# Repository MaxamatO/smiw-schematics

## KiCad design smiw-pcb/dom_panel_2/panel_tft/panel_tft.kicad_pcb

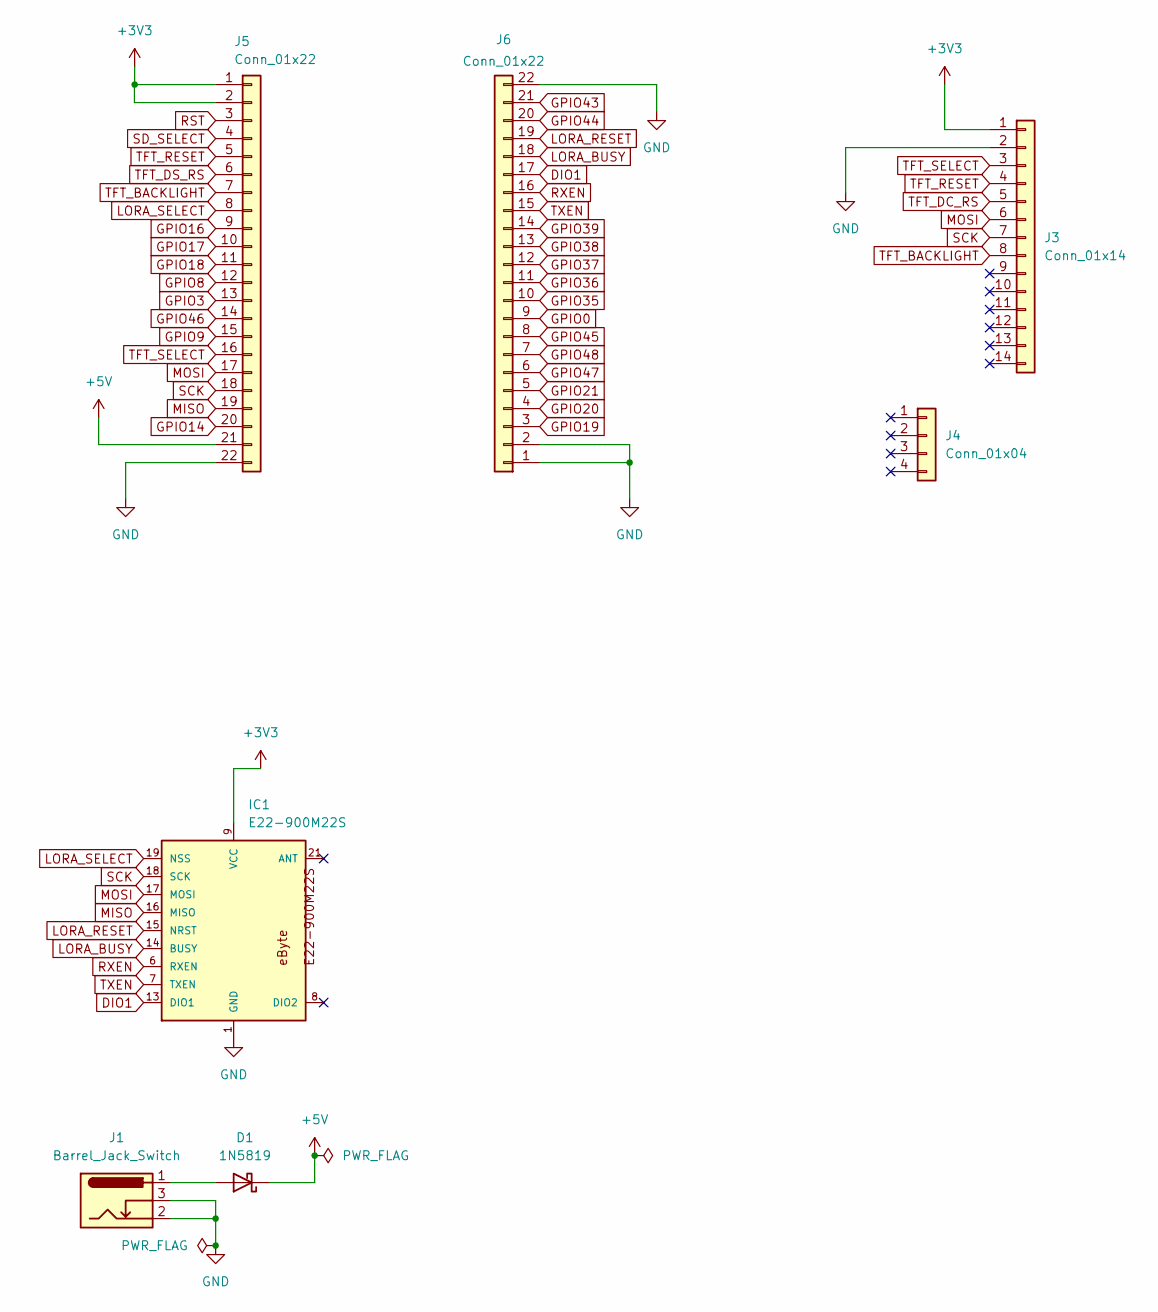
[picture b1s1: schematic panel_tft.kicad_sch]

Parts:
D1: 1N5819; D_DO-41_SOD81_P10.16mm_Horizontal
IC1: E22-900M22S
J1: Barrel_Jack_Switch; BarrelJack_Horizontal
J3: Conn_01x14; PinSocket_1x14_P2.54mm_Vertical
J4: Conn_01x04; PinSocket_1x04_P2.54mm_Vertical
J5, J6: Conn_01x22; PinSocket_1x22_P2.54mm_Vertical

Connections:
+3V3: IC1.9 (VCC), J3.1, J5.1, J5.2
+5V: D1.1 (K), J5.21
DIO1: IC1.13 (DIO1), J6.17
GND: IC1.1 (GND), IC1.2 (GND), IC1.3 (GND), IC1.4 (GND), IC1.5 (GND), IC1.10 (GND), IC1.11 (GND), IC1.12 (GND), IC1.20 (GND), IC1.22 (GND), J1.2, J1.3, J3.2, J5.22, J6.1, J6.2, J6.22
GPIO0: J6.9
GPIO3: J5.13
GPIO8: J5.12
GPIO9: J5.15
GPIO14: J5.20
GPIO16: J5.9
GPIO17: J5.10
GPIO18: J5.11
GPIO19: J6.3
GPIO20: J6.4
GPIO21: J6.5
GPIO35: J6.10
GPIO36: J6.11
GPIO37: J6.12
GPIO38: J6.13
GPIO39: J6.14
GPIO43: J6.21
GPIO44: J6.20
GPIO45: J6.8
GPIO46: J5.14
GPIO47: J6.6
GPIO48: J6.7
LORA_BUSY: IC1.14 (BUSY), J6.18
LORA_RESET: IC1.15 (NRST), J6.19
LORA_SELECT: IC1.19 (NSS), J5.8
MISO: IC1.16 (MISO), J5.19
MOSI: IC1.17 (MOSI), J3.6, J5.17
unnamed: D1.2 (A), J1.1
RST: J5.3
RXEN: IC1.6 (RXEN), J6.16
SCK: IC1.18 (SCK), J3.7, J5.18
SD_SELECT: J5.4
TFT_BACKLIGHT: J3.8, J5.7
TFT_DC_RS: J3.5
TFT_DS_RS: J5.6
TFT_RESET: J3.4, J5.5
TFT_SELECT: J3.3, J5.16
TXEN: IC1.7 (TXEN), J6.15

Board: 2 copper layers, 7 parts (0 on the bottom side), 16 nets, no tracks yet.

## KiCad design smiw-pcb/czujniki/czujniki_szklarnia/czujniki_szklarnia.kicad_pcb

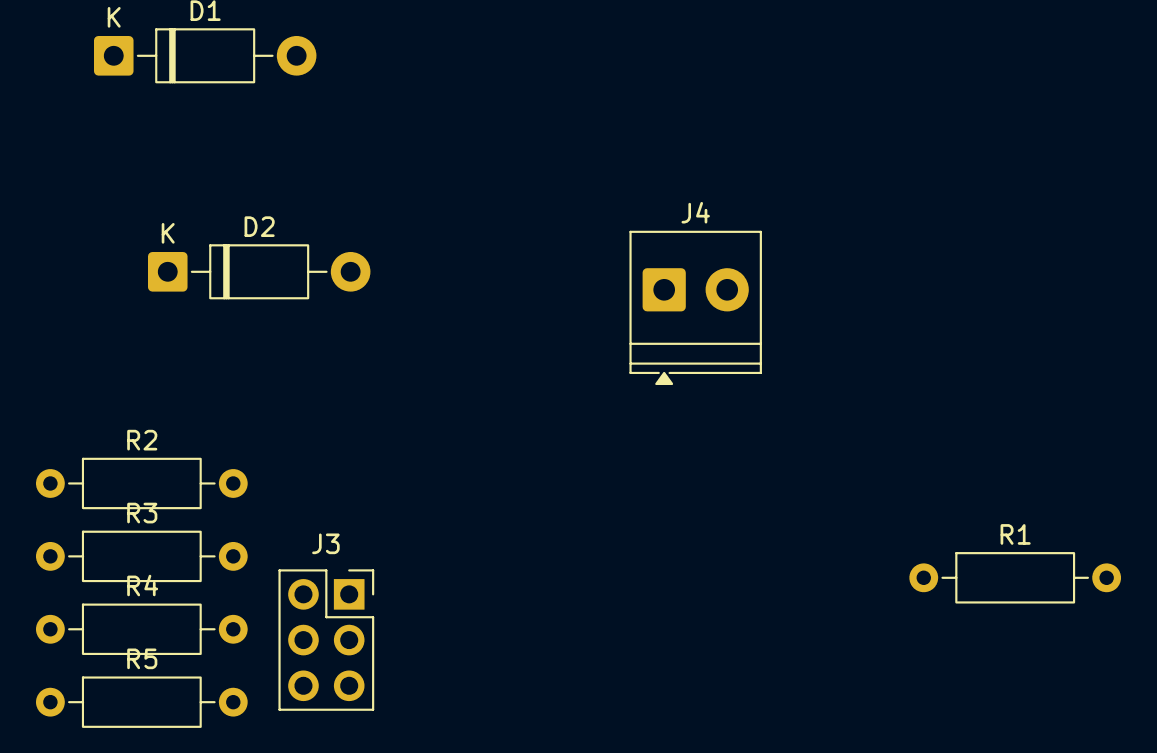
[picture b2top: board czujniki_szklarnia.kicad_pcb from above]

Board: 2 copper layers, 9 parts (0 on the bottom side), 6 nets, no tracks yet.

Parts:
D1, D2: 1N4007; D_DO-41_SOD81_P10.16mm_Horizontal
J3: Conn_02x03_Counter_Clockwise; PinSocket_2x03_P2.54mm_Vertical
J4: Screw_Terminal_01x02; TerminalBlock_Phoenix_PT-1,5-2-3.5-H_1x02_P3.50mm_Horizontal
R1: 4K7; R_Axial_DIN0207_L6.3mm_D2.5mm_P10.16mm_Horizontal
R2, R3: 1K; R_Axial_DIN0207_L6.3mm_D2.5mm_P10.16mm_Horizontal
R4, R5: 100K; R_Axial_DIN0207_L6.3mm_D2.5mm_P10.16mm_Horizontal

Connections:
+3V3: J3.1, R1.2
+24V: D1.1 (K), D2.1 (K)
GND: J3.2, J3.6, R4.1, R5.1
unnamed: R2.2, R5.2
unnamed: R3.2, R4.2
OW: J3.3, R1.1

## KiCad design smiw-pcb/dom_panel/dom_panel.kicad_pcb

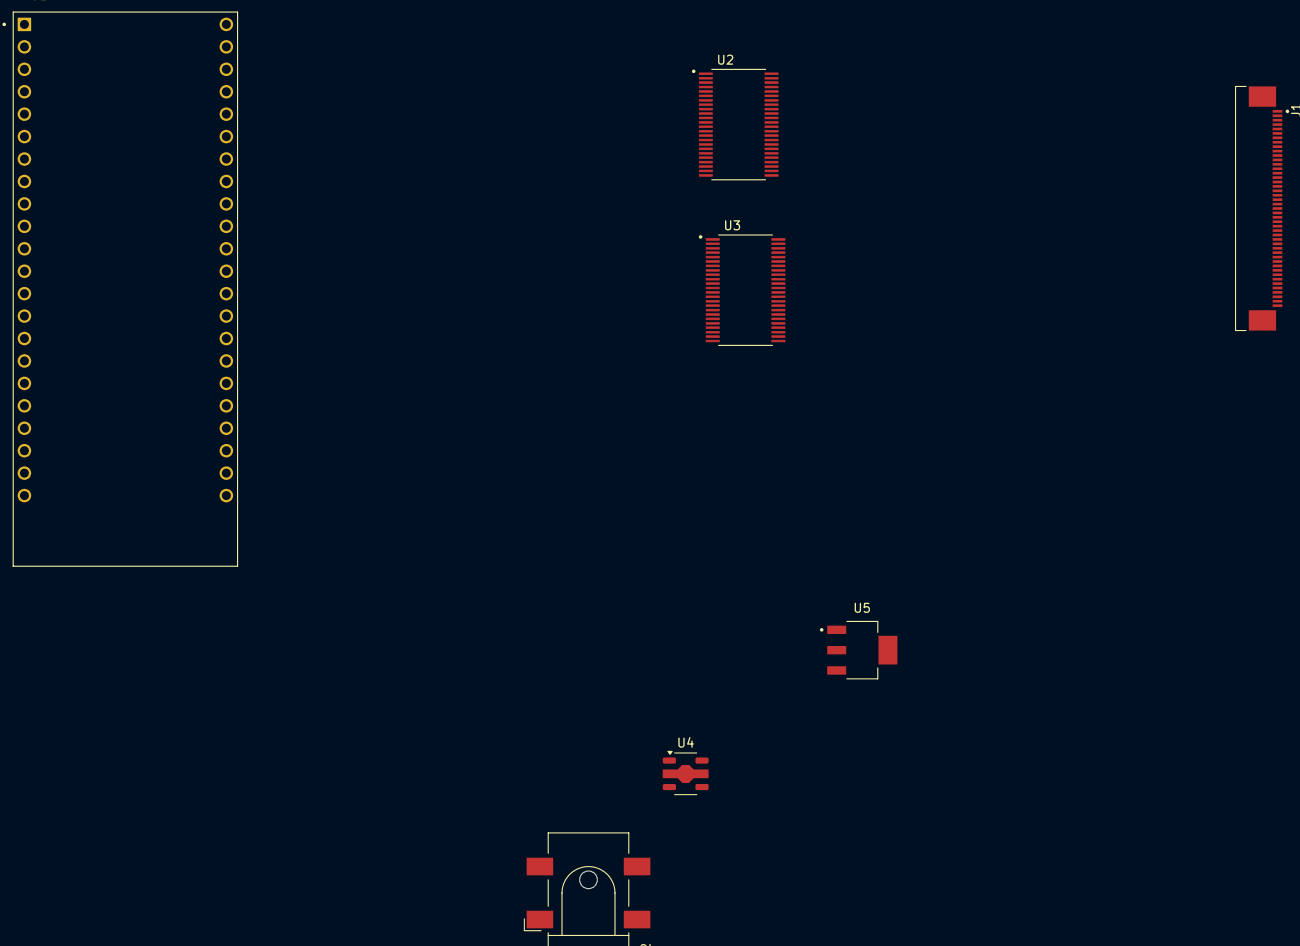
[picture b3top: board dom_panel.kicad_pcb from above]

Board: 2 copper layers, 7 parts (0 on the bottom side), 4 nets, no tracks yet.

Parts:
J1: 4-1734839-5; TE_4-1734839-5
J2: Barrel_Jack_Switch; BarrelJack_CLIFF_FC681465S_SMT_Horizontal
U1: ESP32-S3-DEVKITC-1-N8R8
U2, U3: SN74AVC16T245DGGR; SOP50P810X120-48N
U4: PT4115; SOT-89-5
U5: REG1117A; SOT230P700X180-4N

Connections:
+1V8: U2.7 (VCCB), U2.18 (VCCB), U3.7 (VCCB), U3.18 (VCCB), U5.2 (VOUT), U5.4 (VOUT)
+3V3: U2.31 (VCCA), U2.42 (VCCA), U3.31 (VCCA), U3.42 (VCCA), U5.3 (VIN)
GND: U1.J1_22 (GND3), U1.J3_1 (GND), U1.J3_21 (GND1), U1.J3_22 (GND2), U2.4 (GND), U2.10 (GND), U2.15 (GND), U2.21 (GND), U2.28 (GND), U2.34 (GND), U2.39 (GND), U2.45 (GND), U3.4 (GND), U3.10 (GND), U3.15 (GND), U3.21 (GND), U3.28 (GND), U3.34 (GND), U3.39 (GND), U3.45 (GND), U4.2 (GND), U5.1 (GROUND)
unnamed: J1.S1 (SHIELD), J1.S2 (SHIELD)

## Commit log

2025-12-18 project structure
2025-12-18 Added basic power lines
2026-01-07 wsszystko
